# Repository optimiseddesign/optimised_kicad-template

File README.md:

# Release Notes

This document gives information and history for the following PCB release:

|Item                           |Value                                        |
|-------------------------------|---------------------------------------------|
|Board Name                     |Board Name                                   |
|PCB ID                         |PTXXXX                                       |
|Revision (Layout/PCB)          |1.0                                          |
|Revision (Schematic/BOM)       |1A                                           |
|Release Date                   |YYYY-MM-DD                                   |
|Customer                       |CUSTOMER                                     |

> Note: This PCB release has been designed by Optimised Product Design Ltd, on behalf of the Customer Company.

## PCB Images

Top View:

![alt text][image_top]

Bottom View:

![alt text][image_bottom]

[image_top]: images/ptxxxx_boardname_top.png "Top View"
[image_bottom]: images/ptxxxx_boardname_bottom.png "Bottom View"

## PCB Description

Description Text

## Release History

```
Kevin Bibby / Optimised Product Design Ltd
PTXXXX 1.0 1A
DD/MM/YYYY
-------------
Change1
Change2
Change3
```

```
AUTHOR
VERSION
DD/MM/YYYY
-------------
Previous other version Change1
```

## PCB TO-DO List

The following items are to be done in future for this PCB:

**Major**
- Item

**Minor**
- Item

## Links

- [Official CLIENT-COMPANY website]( https://www.CLIENT-COMPANY.com/ )
- [Official CLIENT-PROJECT link]( https://www.CLIENT-PROJECT.com/ )
- [Kevin Bibby / Optimised Product Design Ltd]( http://www.optimiseddesign.com )

# TODO (both this file, and the PCB template):
- Add Layer names so PDF Print Layers option works
- Add Design Checklist (or in library?)
- Set up default template design rules etc
- Explain project Set Up, and KB consulting involvement
- Release notice/ECN file?
- Release history file? Including explaining handover and version heritage
- Sort out my PCB ID & versions
- (?) Client PCB ID & version
- (?) Client logo
- Add my logo, once designed
- Check enModus OrCAD for other ideas

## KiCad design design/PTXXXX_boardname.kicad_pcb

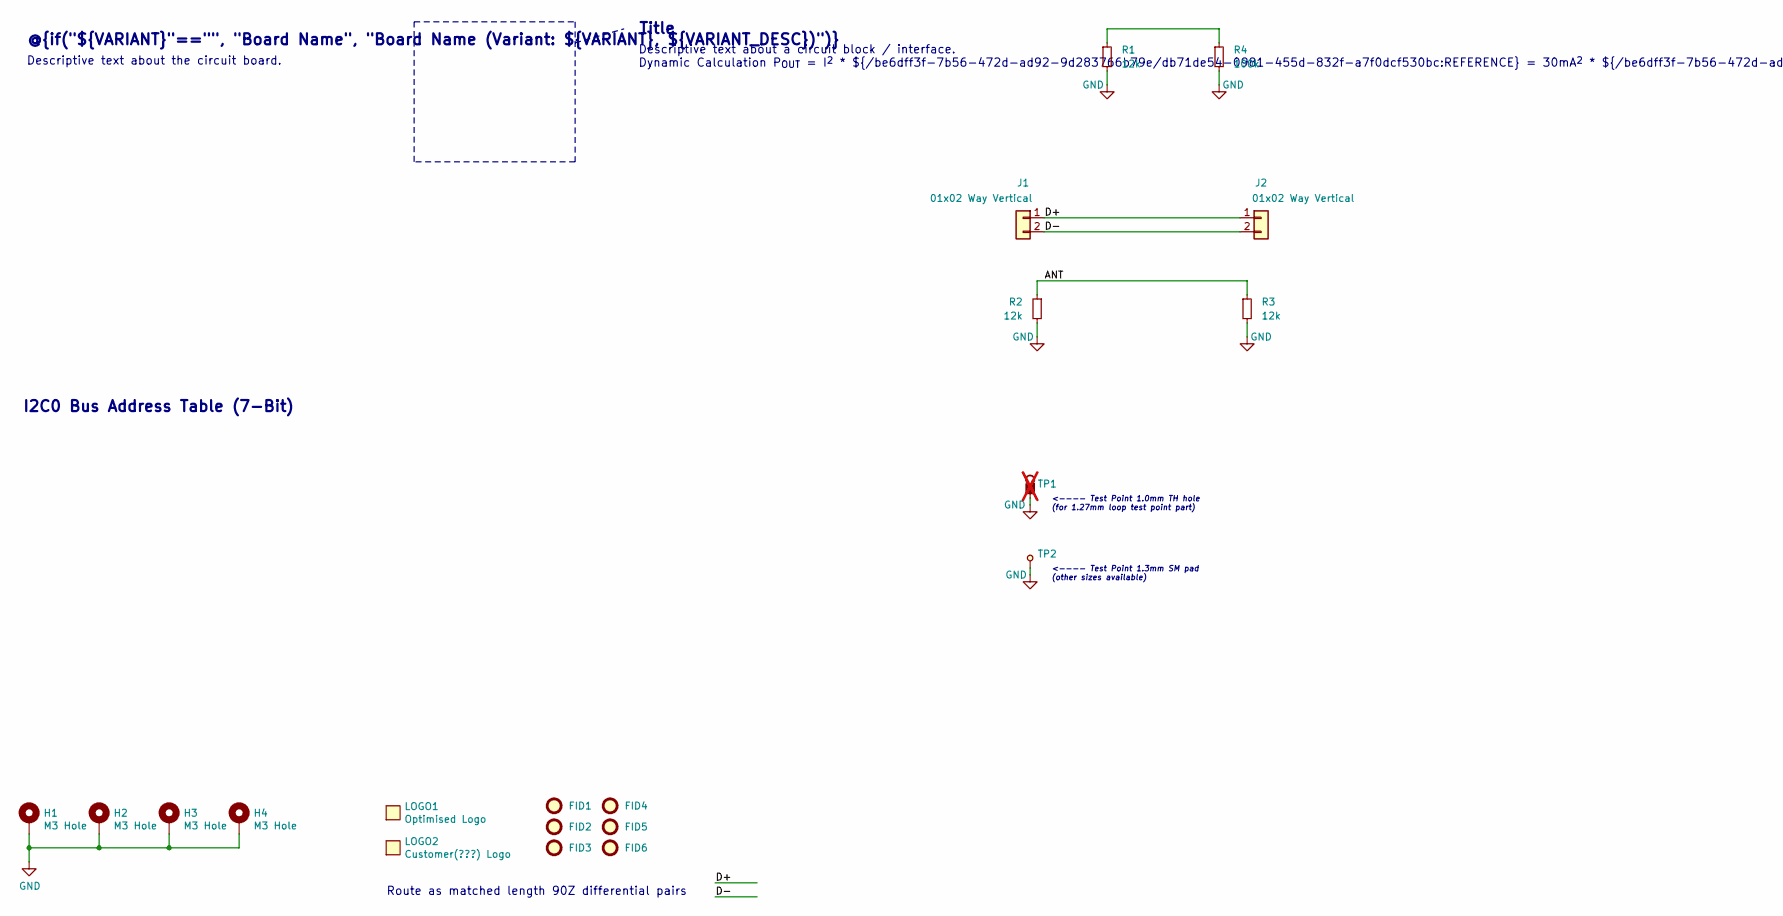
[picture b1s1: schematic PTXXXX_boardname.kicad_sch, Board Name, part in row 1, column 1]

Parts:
FID1, FID2, FID3, FID4, FID5, FID6: Fiducial; Fiducial_1mm_Mask3mm; MPN1 N/A
H1, H2, H3, H4: M3 Hole; MountingHole_3.5mm_Pad_Via; MPN1 N/A
J1, J2: 01x02 Way Vertical; PinHeader_1x02_P2.54mm_Vertical; MPN1 As Appropriate
LOGO1: Optimised Logo; PCB_Silk_Logo_Optimised; MPN1 N/A
LOGO2: Customer(???) Logo; ???; MPN1 N/A
R1, R2, R3: 12k; Resistor_SMD_0603_1608m; MPN1 As Appropriate
R4: 100k; Resistor_SMD_0603_1608m; MPN1 As Appropriate
TP1: TestPoint_TH_Loop_1.27mm_Keystone_5001; MPN1 5001; not fitted
TP2: TestPoint_Pad_1.3mm; MPN1 N/A

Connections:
/ANT: R2.1, R3.1
/D+: J1.1, J2.1
/D-: J1.2, J2.2
GND: H1.1 (1_1), H2.1 (1_1), H3.1 (1_1), H4.1 (1_1), R1.2, R2.2, R3.2, R4.2, TP1.1 (1_1), TP2.1 (1_1)
unnamed: R1.1, R4.1

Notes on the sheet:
<---- Test Point 1.0mm TH hole (for 1.27mm loop test point part)
Route as matched length 90Z differential pairs
I2C0 Bus Address Table (7-Bit)
Title
Descriptive text about the circuit board.
Descriptive text about a circuit block / interface. Dynamic Calculation P_{OUT} = I^{2} * ${/be6dff3f-7b56-472d-ad92-9d283766b79e/db71de54-0981-455d-832f-a7f0dcf530bc:REFERENCE} = 30mA^{2} * ${/be6dff3f-7b56-472d-ad92-9d283766b79e/db71de54-0981-455d-832f-a7f0dcf530bc:VALUE} = @{round(pow(0.030, 2) 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
@{if("${VARIANT}"=="", "${TITLE}", "${TITLE} (Variant: ${VARIANT}, ${VARIANT_DESC})")}
<---- Test Point 1.3mm SM pad (other sizes available)

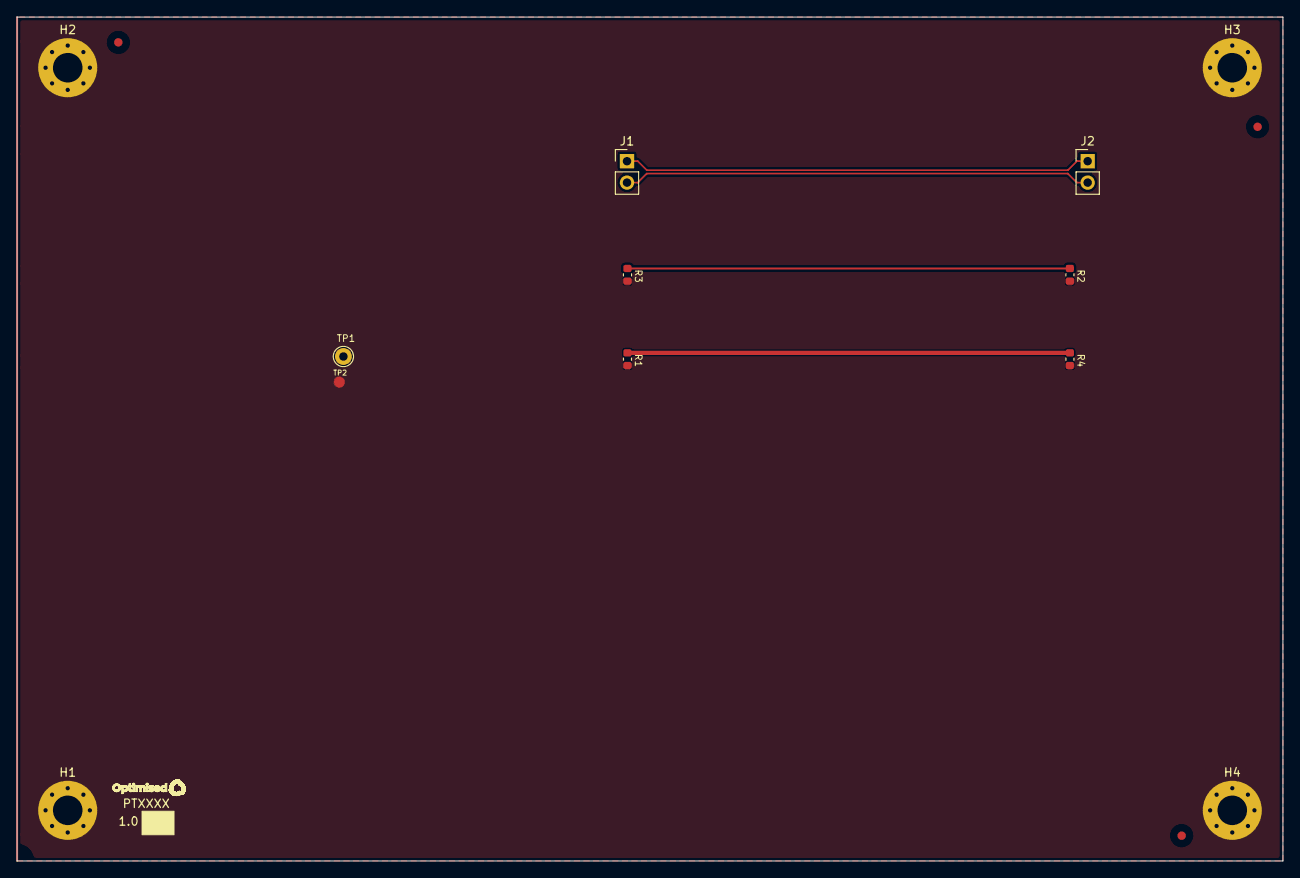
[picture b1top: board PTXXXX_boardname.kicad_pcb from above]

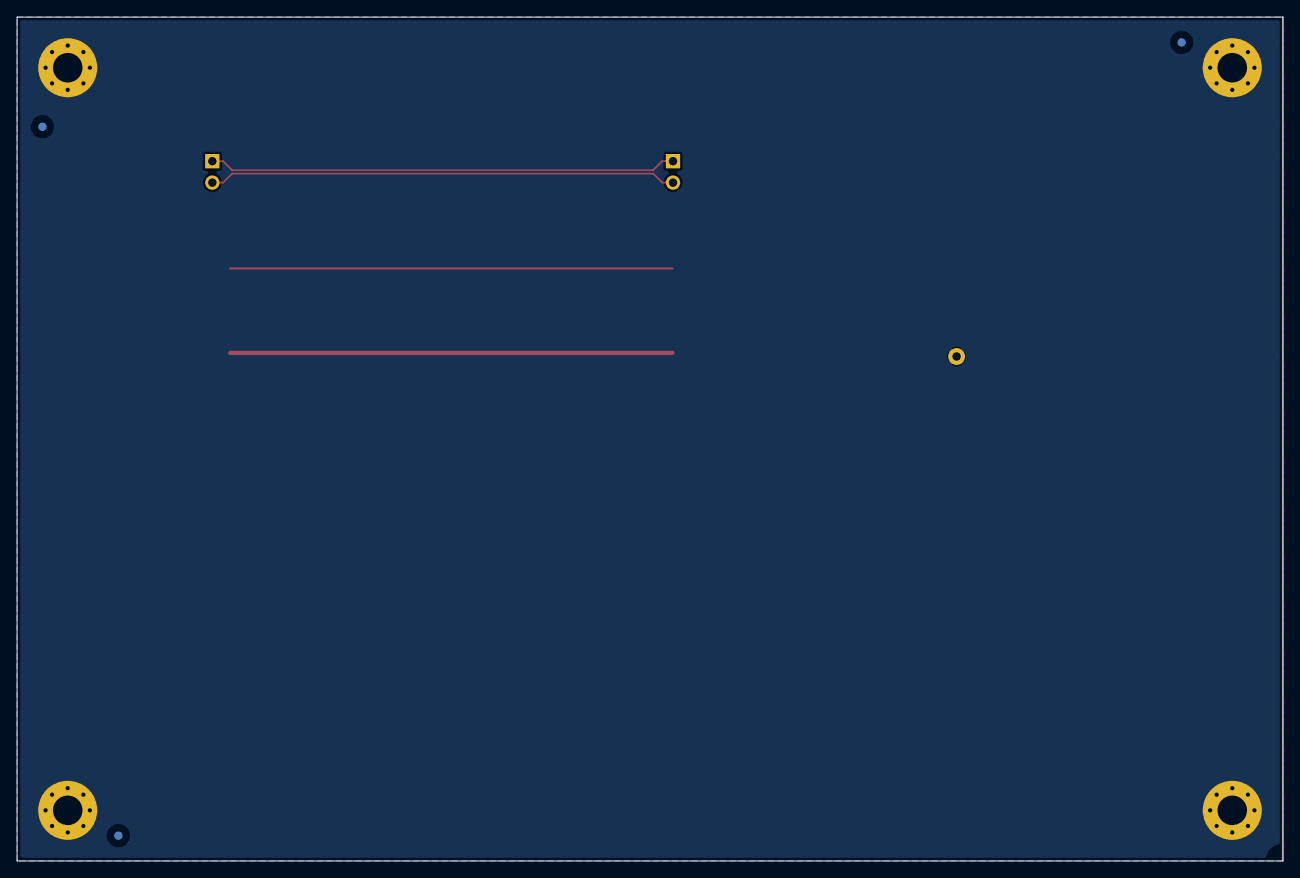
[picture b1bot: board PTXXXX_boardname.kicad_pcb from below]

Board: 4 copper layers, 150.0 x 100.0 mm, 19 parts (3 on the bottom side), 5 nets.

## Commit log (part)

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2019-11-21 added *.sch-bak to ignore removed *.xml and *.csv exported BOM files from ignore
2019-11-22 adding blank kicad project, including reference to test local symbol library '_kb_relays_switches'
2019-11-22 added company common libraries as git submodule
2019-11-22 updating submodule libraries
2019-11-22 changed URL for submodule to be full rather than relative to my local copy
2019-11-22 removed sym-lib-table from this repo, library tables are better in the symbol/footprint libraries themselves
2019-11-22 updated libraries submodule
2019-12-20 set up simple folder structure added blank new KiCAD project files
2019-12-20 added dummy values to schematic page setup
2019-12-20 added submodule for KBconsulting KiCAD libraries
2019-12-20 move submodule KiCAD libaries into design directory, to be a subdirectory of KiCAD project
2019-12-20 moved KiCAD files one directory up... ...(removed PTXXXX_boardname directory which I didn't realise KiCAD had made
2019-12-20 added schematic titleblock link, from one in KiCAD libraries submodule
2019-12-20 added latest Schematic & PCB Titleblock test titleblocks as default
2019-12-20 set default Schematic/BOM revision to '1A' set default PCB/Layout revision to '1.0'
2019-12-21 changed titleblock filename added/modified default page setup for new titleblock updated to latest library submodule to get latest titleblock
2019-12-21 added first version of work-in-progress release notes / Readme file
2019-12-21 modified readme to include link to mine & client websites removed a couple bullet point TODO items for ease of template use
2019-12-21 updating README with more info on board and better formatting added bullet points to web links to avoid displaying on one line as some website did
2019-12-23 added /images/ and /mechanical/ folders updated readme to add image reference, and release history template updated TODO at end
2020-02-14 specified 'branch = master' for submodule to try solve issue of it being checked out in detached HEAD state
2020-02-14 specified 'update = rebase' for submodule to try solve issue of it being checked out in detached HEAD state
2020-02-14 test advancing submodule one commit (inconsequential to template) want to see if this solves pull meaning submodule is in detatched HEAD state
2020-03-17 updated readme slightly to use 'Customer' instead of 'Client' updated kbconsulting library submodule to the latest
2020-04-08 updated library to latest, updated titleblocks and dates
2020-04-08 copied latest project sym-lib-table and fp-lib-table from updated kb consulting library
2020-04-08 added readme on how to successfully use this template
2020-05-02 added 4off M3 mounting holes as default added useful descriptive text as default updated library refs to latest
2020-05-04 added PCB outline for board size 150mm x 100mm with 1.5mm margin changed board setup and design rules etc... ...changed board type to 4-layer, components both sides, removed Adhesive layers ...set mi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
2020-05-04 added name & description text for every PCB layer added defined track widths (0.25mm to 3mm) & via sizes (0.3/0.6mm & 0.5/0.9mm)
2020-05-04 added silkscreen logo & PCB ID (locally in PCB design, not using footprints) added GND copper planes on all 4 layers (0.4mm clearance/0.25mm for same-net) updated library refs updated template design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
2020-06-18 added fabrication PCB specification text to F.Fab layer moved board, origins etc to give more space
2020-06-18 changed differential pair description to use 'Z' rather than 'R' for impedance KiCAD removed cache library on its own updated library ref to latest
2020-06-18 added simple PCB stackup drawing on F.Fab layer added dimensions on Dwgs.User as example, updated fab text to match
2020-06-29 added Signal/GND/PWR names on layer stackup F.Fab drawing
2020-10-22 modified readme.md for Optimised Product Design branding added spaces before/after links as didn't work when clicked in Notepad++
2020-10-28 modified template KiCAD project to use new OptimisedPD titleblock changed PCB silkscreen text from KBconsulting to OptimisedPD updated library ref to use new OptimisedPD titleblock
2020-10-28 minor changes to readme text on how to create new project repo from template repo
2020-10-28 added my new resistors footprint library to default template library table
2021-03-23 updating submodule URL after github username rename updating template readme after template repo rename
2021-03-23 changing to new kicad libraries submodule name / path
2021-03-23 updated to latest kicad library also updates for latest naming 'optimised_kicad-libraries'
2021-03-23 updated sym-lib-table and fp-lib-table to latest... ...for new optimised_kicad-library name
2021-03-29 added LOGO1 for optimised silkscreen logo corrected titleblock reference, was still kbconsulting re-imported to PCB and placed optimised logo deleted silkscreen optimised text
2021-09-20 added new triac-thyristor library to project sym-lib-table updated library ref for new library and to latest new parts
2021-12-27 updated library repo to latest
2021-12-27 updated to KiCAD v6.0.0 (incl official libraries), was 5.1.10... ...opened and converted schematic & project, not done PCB yet or reimported ...updated sym-lib-table to new version ...updated library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
2022-01-13 converted kicad PCB layout to v6.0.0 (open and re-save)... ...re-annotated schematic, re-imported netlist to PCB ...NOTE: netlist import message "Remove H1 'exclude from BOM' fabrication attribute" f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
2022-01-13 updated footprints in from library updated fp-lib-table for v6 updated library ref for updated footprints
2022-01-13 updated/changed settings for v6... ...project, schematic & pcb ...page settings, board setup, schematic setup & preferences ...includes setting new stackup feature to match F.Fab text ...fixed pcb F.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
2022-01-13 changed to 0.20/0.20mm track/gap design rules match F.Fab text ...though F.Fab text previously had gap less than design rules ...picked new sensible based on Qucs studio calc 89.3ohm Zdiff
2022-01-19 fixes for edge clearance issue in v6... ...moved 'Margin' line to Eco2 layer ...(Margin interferes with copper in v6) ...changed Margin layer text from "Board Edge Placement Margin" ...now text "Boar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
2022-02-01 added Fiducials FID1-6 using new library part... ...3off top, 3off bottom, 1mm/3mm mask default but 2mm available ...annotated, netlisted, placed in PCB updated library ref for latest
2022-02-02 updated library ref for latest updated footprints
2022-04-21 updated titleblock (and rest of part library)... ...now has "reviewer" field added ...Author/Reviewer now uses Comment2/Comment3 page settings ...sponsored by Mr Stevie Janowski and Sir Long Johnson
2022-05-26 updated library ref for latest (BOM fit_field)
2022-05-26 updated instructions for personal access token
2022-05-26 updated readme for LTD company change
2022-05-26 added author/reviewer name placeholder text to pcb titleblock
2022-05-31 updated instructions after testing Github creating from template
2023-07-31 changed default dimension text to 2dp (was 4dp) changed default dimension arrow to 1.0mm (was 1.27mm) changed default dimension offset to 0mm (was 0.5mm) updated to latest library version
2023-08-01 added pcb editor custom layer visibility views... *Fabrication - Bottom *Fabrication - Top *Layout - Bottom *Layout - Top *Silkscreen - Bottom *Silkscreen - Top
2023-08-08 ****Convert v7 KiCAD format for template kicad project... ...simply opened & re-saved schematic & layout ...also update libraries to use KiCAD v7 converted
2023-08-08 updated page dates, re-netlisted edited and saved schematic & layout settings set min connection (new DRC to 0.2mm same as min gap) set min mask to copper as 0.05mm (new DRC)
2023-08-10 named pcb ground planes added schematic dashed circuit block bbounding box updated library ref for heatsink/solid centre pads **WIP** added useful custom DRC rules... ...note, pending question on cra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
2023-08-14 converted USB diff pair indicator to dashed/dotted line rectangle
2023-08-17 added DRC rule to stop vias in SMD pads... ...other custom DRC rule from v7.0.0 release notes ...also resolved DRC crash issue (fixed in v7.0.7) added comments to clarify first rule is not a DRC!... 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
2023-10-25 updated library to latest renames symbol library ic-microcontroller to ic-processor adds modules-plugin symbol library
2023-12-09 added default part field names to project updated library ref to latest
2024-02-28 added default TG135 PCB FR4 spec for 135C glass transition temp
2024-04-13 updated kicad to v8.0.1 and re-saved (intermediate v7.0.11 update didn't change anything)
2024-04-13 updated library link after libraries updated to v8.0.1
2025-01-07 updated kicad libraries to latest incl 2025 copyright date
2025-02-14 update fp-lib-table, fixes modules.pretty error updaed library ref to latest
2025-02-14 re-save in kicad v8.0.8 format, v minor
2025-07-02 QoL Quality of Life changes: added extra readme titleblock space added customer logo part arrange BOM order in schematic symbol fields table added GND test point styles (hole and pad) reduced solderm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
2025-09-02 re-save KiCAD project in v9.0.4 also re-import all symbols & footprints, re-netlist includes update of kicad libraries to v9
2025-09-02 update library ref (missing one footprint ref update)
2025-11-22 migrate DNF 'FitPart'; use KiCAD v9 DNP field... ...or exclude from BOM (depending on part) updated all parts from library also removed FitPart from schematic field names update library ref for lates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
2025-11-22 added schematic table example (I2C Bus Table) replaced layout fabrication text with table
2026-01-21 corrected layer name text to User.Eco1/2 updated titleblock dates
2026-02-04 added KiCAD *.lck lock files to ignore
2026-02-17 embed Optimised worksheet in schematic OptimisedPD_Titleblock.kicad_wks
2026-02-17 added 90Z_DIFF net class to template updated template to use net directive set diff pair highlight colour to light blue/cyan
2026-02-17 added layer pair presets for 4L board
2026-02-17 embed Optimised worksheet in layout OptimisedPD_Titleblock.kicad_wks missed layout titleblock from previous commit
